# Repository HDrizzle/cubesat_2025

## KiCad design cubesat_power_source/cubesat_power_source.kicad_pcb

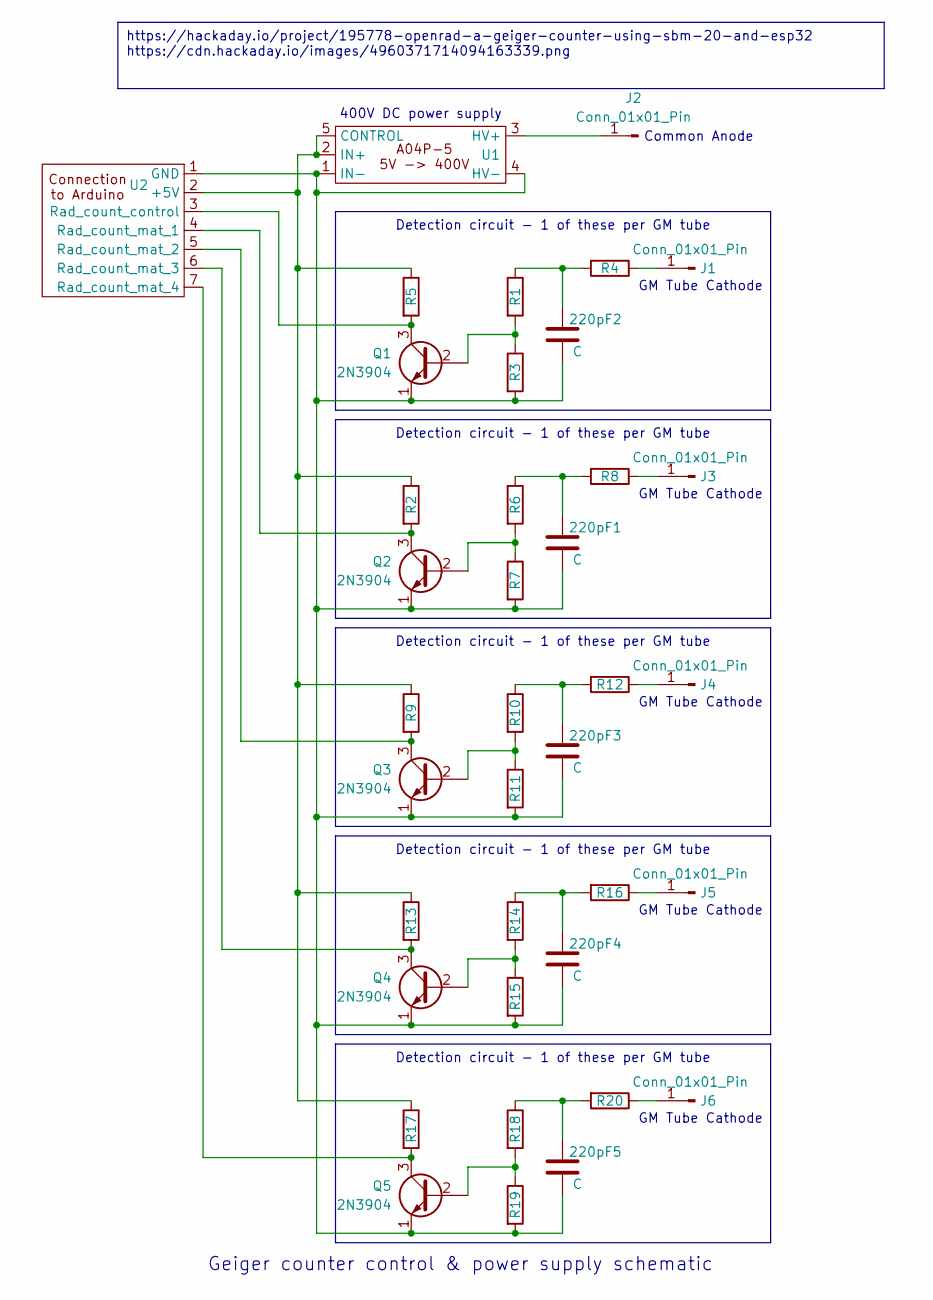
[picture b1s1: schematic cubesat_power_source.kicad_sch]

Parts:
220pF1, 220pF2, 220pF3, 220pF4, 220pF5: C; C_Disc_D4.3mm_W1.9mm_P5.00mm
J1, J2, J3, J4, J5, J6: Conn_01x01_Pin; PinHeader_1x01_P2.54mm_Vertical
Q1, Q2, Q3, Q4, Q5: 2N3904; TO-92_Inline
R1, R6, R10, R14, R18: 22K; 0.4_pitch_resistor
R2, R5, R9, R13, R17: 10K; 0.4_pitch_resistor
R3, R7, R11, R15, R19: 100K; 0.4_pitch_resistor
R4, R8, R12, R16, R20: 4.7M; 0.4_pitch_resistor
U1: xp_power_dc_dc_converter
U2: PinHeader_1x07_P2.54mm_Horizontal

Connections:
unnamed: 220pF1.1, R6.1, R8.2
unnamed: 220pF2.1, R1.1, R4.2
unnamed: 220pF3.1, R10.1, R12.2
unnamed: 220pF4.1, R14.1, R16.2
unnamed: 220pF5.1, R18.1, R20.2
unnamed: J1.1, R4.1
unnamed: J2.1, U1.3 (HV+)
unnamed: J3.1, R8.1
unnamed: J4.1, R12.1
unnamed: J5.1, R16.1
unnamed: J6.1, R20.1
unnamed: Q1.2 (B), R1.2, R3.1
unnamed: Q1.3 (C), R5.2, U2.3 (Rad_count_control)
unnamed: 220pF1.2, 220pF2.2, 220pF3.2, 220pF4.2, 220pF5.2, Q1.1 (E), Q2.1 (E), Q3.1 (E), Q4.1 (E), Q5.1 (E), R3.2, R7.2, R11.2, R15.2, R19.2, U1.1 (IN-), U1.4 (HV-), U2.1 (GND)
unnamed: Q2.2 (B), R6.2, R7.1
unnamed: Q2.3 (C), R2.2, U2.4 (Rad_count_mat_1)
unnamed: Q3.2 (B), R10.2, R11.1
unnamed: Q3.3 (C), R9.2, U2.5 (Rad_count_mat_2)
unnamed: Q4.2 (B), R14.2, R15.1
unnamed: Q4.3 (C), R13.2, U2.6 (Rad_count_mat_3)
unnamed: Q5.2 (B), R18.2, R19.1
unnamed: Q5.3 (C), R17.2, U2.7 (Rad_count_mat_4)
unnamed: R2.1, R5.1, R9.1, R13.1, R17.1, U1.2 (IN+), U1.5 (CONTROL), U2.2 (+5V)

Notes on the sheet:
Detection circuit - 1 of these per GM tube
https://hackaday.io/project/195778-openrad-a-geiger-counter-using-sbm-20-and-esp32 https://cdn.hackaday.io/images/4960371714094163339.png
Geiger counter control & power supply schematic
GM Tube Cathode
400V DC power supply
Common Anode

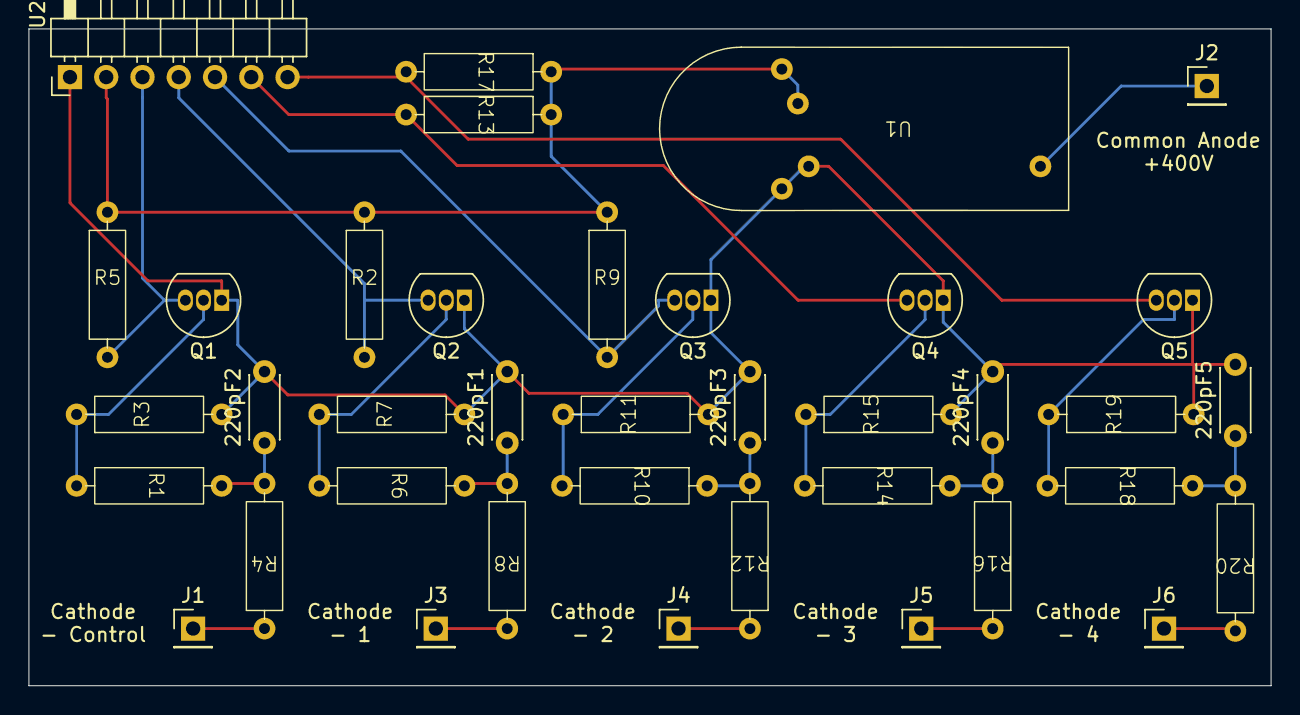
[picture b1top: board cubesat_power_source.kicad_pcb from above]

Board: 2 copper layers, 87.0 x 46.0 mm, 38 parts (0 on the bottom side), 23 nets.

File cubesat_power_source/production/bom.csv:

Designator,Footprint,Quantity,Value,LCSC Part #
"220pF1, 220pF2, 220pF3, 220pF4, 220pF5",C_Disc_D4.3mm_W1.9mm_P5.00mm,5,C,
"J1, J2, J3, J4, J5, J6",PinHeader_1x01_P2.54mm_Vertical,6,Conn_01x01_Pin,
"Q1, Q2, Q3, Q4, Q5",TO-92_Inline,5,2N3904,
"R1, R10, R14, R18, R6",0.4_pitch_resistor,5,22K,
"R11, R15, R19, R3, R7",0.4_pitch_resistor,5,100K,
"R12, R16, R20, R4, R8",0.4_pitch_resistor,5,4.7M,
"R13, R17, R2, R5, R9",0.4_pitch_resistor,5,10K,
U1,xp_power_dc_dc_converter,1,~,
U2,PinHeader_1x07_P2.54mm_Horizontal,1,~,

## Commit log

2025-04-17 PCB files and last years arduino code
2025-04-18 Fixed old code formatting, added geiger counter logic to new ccode
2025-04-18 doing stuff
2025-05-01 Removed 15 min start delay and finished geiger counter logic
2025-05-01 Box for geiger counters
2025-05-02 Easton code
2025-05-02 About to get rid of serial1
